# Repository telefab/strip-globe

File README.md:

LED strip-based, FPGA-powered POV globe
===

Documentation
---

Documentation is [available on Instructables](http://www.instructables.com/id/Globe-of-persistence-of-vision/).

Source structure
---

* `app_sources`: sources of programs running on the globe
* `board`: power board Eagle model
* `fpga_sources`: VHDL files for the FPGA
* `Solidworks`: model for the physical design
* `zybo_project`: integration on the Zybo board. The Vivado project references the `fpga_sources` files

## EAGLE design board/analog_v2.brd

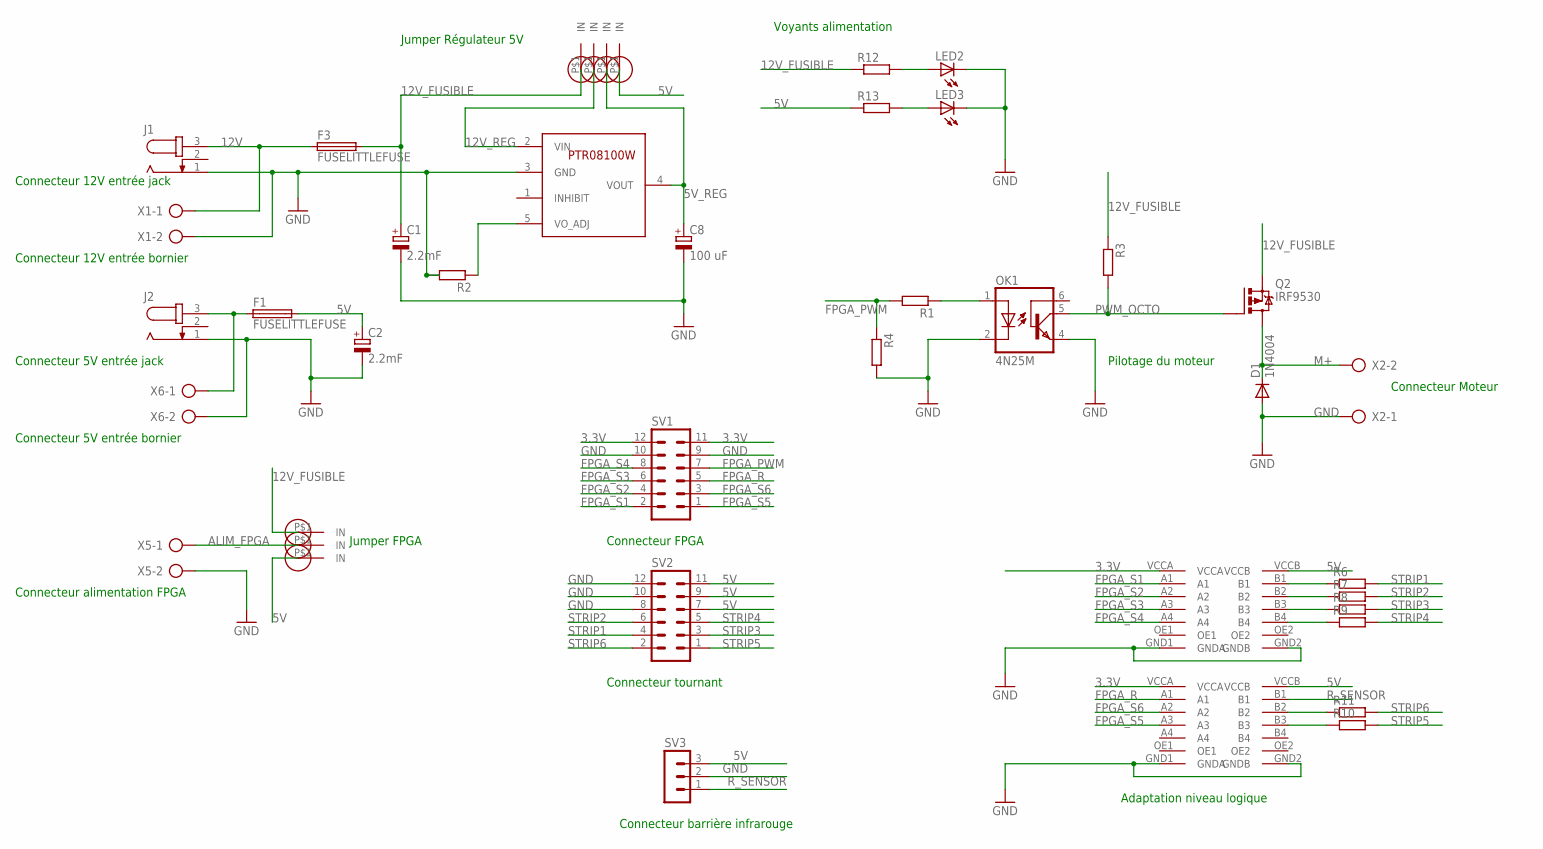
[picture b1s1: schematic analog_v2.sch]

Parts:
C1, C2: 2.2mF; E7,5-16
C8: 100 uF; E2,5-7
D1: 1N4004; DO41-10
F1, F3: FUSELITTLEFUSE; LITTLEFUSE
J1, J2: JACK-PLUG1; SPC4078
LED2, LED3: LED5MM
OK1: 4N25M; DIL06; MPN 4N25-M
Q2: IRF9530; TO220BV
R1, R2, R3, R4, R6, R7, R8, R9, R10, R11, R12, R13: R-EU_0207/10; 0207/10
SV1, SV2: MA06-2
SV3: MA03-1
U2: PTR08100W
U$1, U$2: TXB0104
U$3, U$4, U$5, U$6, U$7, U$10, U$12: JUMPER_CONNECTOR
X1, X2, X5, X6: AK500/2

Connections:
3.3V: SV1.11, SV1.12, U$1.VCCA, U$2.VCCA
5V: C2.+, F1.2, R13.1, SV2.7, SV2.9, SV2.11, SV3.3, U$1.VCCB, U$2.VCCB, U$5.P$1, U$10.P$1
5V_IN: F1.1, J2.3, X6.1
5V_REG: C8.+, U2.4 (VOUT), U$12.P$1
12V: F3.1, J1.3, X1.1
12V_FUSIBLE: C1.+, F3.2, Q2.S, R3.1, R12.1, U$3.P$1, U$6.P$1
12V_REG: U2.2 (VIN), U$7.P$1
ALIM_FPGA: U$4.P$1, X5.1
FPGA_PWM: R1.2, R4.1, SV1.7
FPGA_R: SV1.5, U$2.A1
FPGA_S1: SV1.2, U$1.A1
FPGA_S2: SV1.4, U$1.A2
FPGA_S3: SV1.6, U$1.A3
FPGA_S4: SV1.8, U$1.A4
FPGA_S5: SV1.1, U$2.A3
FPGA_S6: SV1.3, U$2.A2
GND: C1.-, C2.-, C8.-, D1.A, J1.1, J2.1, LED2.K (C), LED3.K (C), OK1.2 (C), OK1.4 (EMI), R2.2, R4.2, SV1.9, SV1.10, SV2.8, SV2.10, SV2.12, SV3.2, U2.3 (GND), U$1.GND1 (GNDA), U$1.GND2 (GNDB), U$2.GND1 (GNDA), U$2.GND2 (GNDB), X1.2, X2.1, X5.2, X6.2
M+: D1.C, Q2.D, X2.2
PWM_OCTO: OK1.5 (COL), Q2.G, R3.2
RES_LED_5V: LED3.A, R13.2
RES_LED_12V: LED2.A, R12.2
RES_OCTO: OK1.1 (A), R1.1
R_SENSOR: SV3.1, U$2.B1
R_STRIP_1: R6.1, U$1.B1
R_STRIP_2: R7.1, U$1.B2
R_STRIP_3: R8.1, U$1.B3
R_STRIP_4: R9.1, U$1.B4
R_STRIP_5: R10.1, U$2.B3
R_STRIP_6: R11.1, U$2.B2
STRIP1: R6.2, SV2.4
STRIP2: R7.2, SV2.6
STRIP3: R8.2, SV2.3
STRIP4: R9.2, SV2.5
STRIP5: R10.2, SV2.1
STRIP6: R11.2, SV2.2
VO_ADJ: R2.1, U2.5 (VO_ADJ)

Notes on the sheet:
Connecteur FPGA
Connecteur tournant
Connecteur barrière infrarouge
Connecteur Moteur
Connecteur 12V entrée jack
Jumper Régulateur 5V
Connecteur 5V entrée jack
Connecteur 12V entrée bornier
Connecteur alimentation FPGA
Voyants alimentation
Jumper FPGA
Connecteur 5V entrée bornier
Adaptation niveau logique
Pilotage du moteur

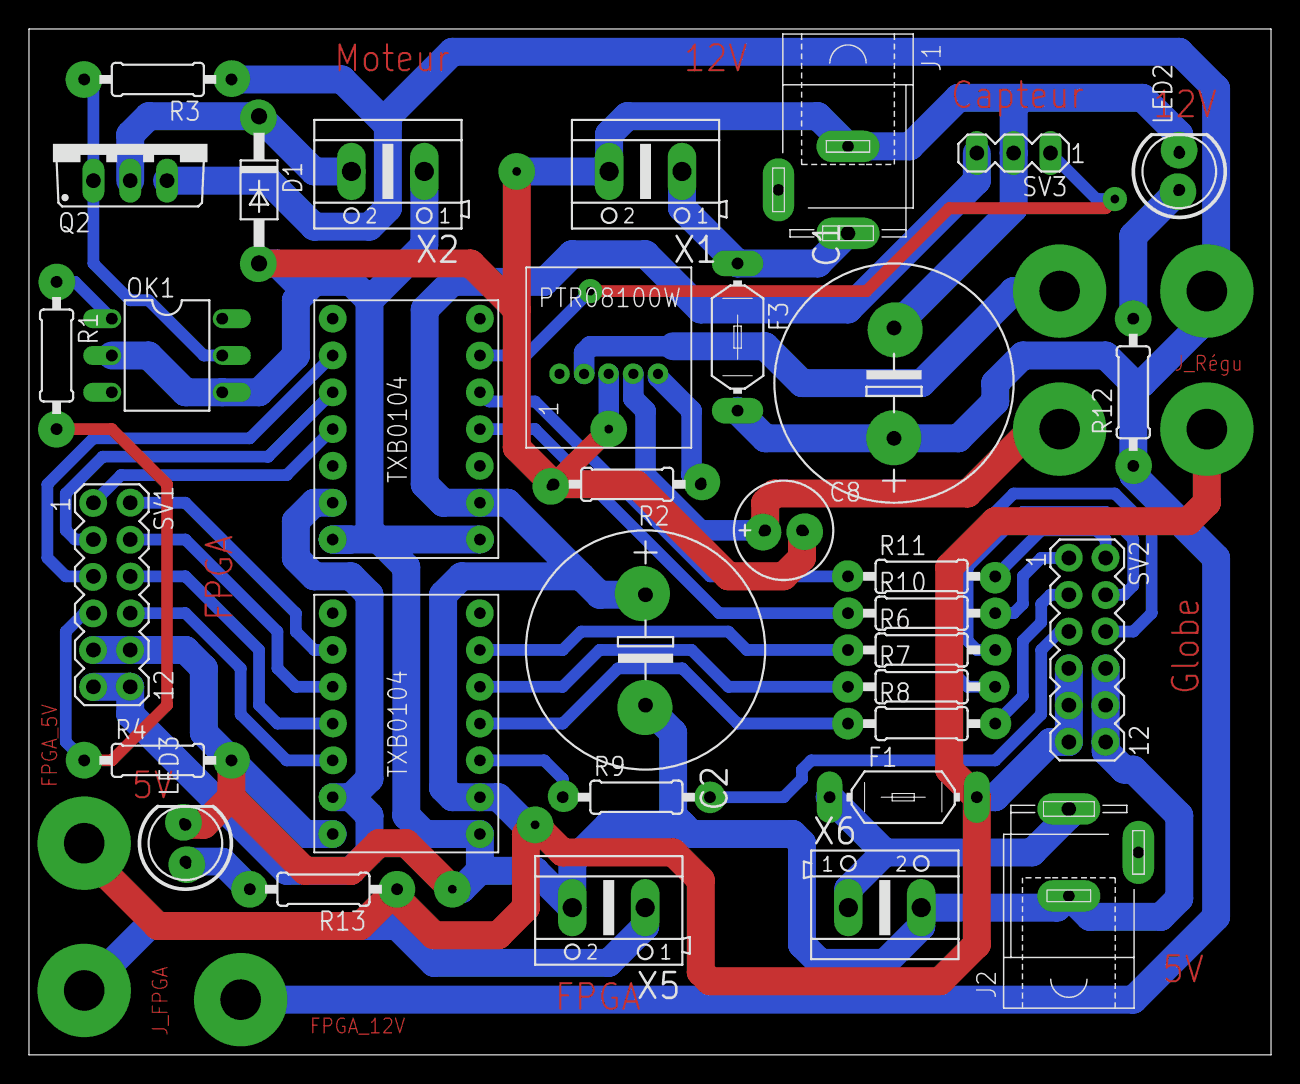
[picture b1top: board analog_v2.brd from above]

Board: 2 copper layers, 85.7 x 70.8 mm, 41 parts (0 on the bottom side), 36 nets.

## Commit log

2014-11-24 Version 0.0 This commit only contains the motor controller
2014-11-25 Version 0.2 Ajout de la carte d'extension pour le globe
2014-11-27 Projet Globe Version 0.3 Fichier de test pour allumer les leds en bleu, blanc et rouge.
2014-11-27 Projet S5 Globe Version 0.4 fichier pour Test.
2014-12-02 Projet S5 Globe Version 0.5 Nouvelle version de la carte d'extension du FPGA
2015-01-15 ProjetS5 Globe V3.0 Globe avec partie affichage fonctionnelle
2015-02-05 Projet Globe V0.5 Synchro added
2015-02-08 Globe working for the zybo board
2015-02-13 synchronisation ajoutée
2015-02-13 globe fonctionnant avec la synchro et les deux frame buffer + le .bit
2015-02-24 Projet S5 Globe V2.5 Ajout des fichiers solidworks et des drivers moteurs
2015-04-07 Sources VHDL de L'IP
2015-05-03 Cleaned up sources, added new strip code.
    This code has been used successfuly at Maker Faire St Malo
    It requires a double check, to be done soon.
2015-05-06 Project: Globe of persistence of vision
    Adds the applications and drivers sources, the solidworks modelisations
    and the config files for setting up the Linux
2015-05-10 The globe of persistence of vision
    The application sources have been corrected and adapted to the new globe
2015-05-10 The globe of persistence of vision
    Addresses of the devices modified to correspond to the new globes' ones
2015-05-18 Updated apps sources for the new globe
    Added the drawing application by Tristan Gouge
2015-05-19 Updated the README
2015-07-10 Creation of a web-interface to control the globe
2015-07-10 Ajout du support de l'internationalisation
2015-07-10 Revert "Creation of a web-interface to control the globe"
    This reverts commit 54b8d7a401a033cc3ec72cbd1f2ea4d24377c6e0.
2015-07-10 Web Interface is more pretty. Oh sorry, less ugly.
2015-10-08 Made the web interface simpler to use
    Removed the input at load
    Added pre-selected colors
    Simplified labels
    Made the drawing a bit bigger
    Tried to make painting detection more robust
2015-10-10 Experimental webcam app
    Display image from the webcam on the globe
2016-09-28 Improved webcam, added snake
2016-10-28 Small fixes
